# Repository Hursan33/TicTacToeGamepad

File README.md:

# TicTacToeGamepad

## TBD 
Test new version of code, assemble the integrated arduino version, upload edited case

## 1 Introduction
This project is an implementation of a Tic Tac Toe game using both hardware and software. The
purpose of the project was to practice working with an 8-bit mcu on register level, but I worked on it more and created a standalone version.
## 2 Materials and technologies
* MCU (I used Avr curiosity nano for school and an Arduino pro micro for standalone)  
* 9x Keyboard switches  
* 9x SK6812MINI-E LEDs  
* 3x 100uF capacitors  
* 1x 330r resistor  
  
The game itself is played on a 3x3 playing field made from keyboard switches, which are soldered onto
a PCB I designed. The PCB sits in a 3D printed case.

## 2 Functions
The game uses addressable LEDs to show the board state. Each player has their own color, which is
shown on the fields the player has occupied. After the game is over, whether it was a draw or a player
won, there is an animation and 5 second delay, after which the game restarts. The first player to act
is decided by which player won the last game, or which player went last. There are 2 possible game
modes:  

* Classic  
* 3-mark rule  

Both game modes can be played in single player, which replaces the second player with a bot.
### 2.1 Classic
This game mode uses the classic rules of a 3x3 tic tac toe game. The player wins by putting 3 marks
in a row, column or diagonal. After the board is filled and no player has won, the game is declared as
a draw.
1
### 2.2 3-mark rule
Here each player only gets 3 marks. After that they must move their oldest mark to a new position.
In this game mode there is no draw, a player must win to end the game. The moving mark is shown
by being dimmer than the rest.
### 2.3 Bot
The bot uses a simple algorithm to decide which space it wants to occupy.
1. Checks if a win is possible, then it places the mark there.  
2. Checks if the player can win, then it blocks the player.  
3. If the center is free, it puts the mark there.  
4. Checks every corner in a random order and occupies it if possible.  
5. Checks every side field in a random order and occupies it if possible.

In the 3-mark rule, when checking if the player can win, it also remembers which mark the player is
moving. This ensures that the bot blocks the correct field.
### 3.4 Ending animation
After the game ends, either by a player winning or a draw, there is an animation played. The animation
lights up the LEDs in a “2” shape with the color of the winning player, or in the case of a draw with
the “draw” color.
## 3 Costumizations
There are a few customizations in the game. First, the game mode and if the bot is active can be
set. The colors of each player and draw are also customizable, using RGB format. The dimness of the
moving mark is also possible to change.
To change these settings these macros can be modified in the “config.h” file:

* GAME_MODE – 1 (3-mark rule) or 0 (Classic).  
* BOT – 1 (Bot is turned on) or 0 (Bot is off).  
* PLAYER_N_COLOR and DRAW_COLOR – has this syntax (Color) R, G, B, you replace the R, G, B
with the corresponding colors of the value. Player colors and draw color all have to be different
otherwise an error occurs.  
* DIM_DIV – the amount by which the values of the color are divided, e.g. DIM_DIV 16 makes the
LEDs be 1
16 of their brightness.  

If there were changes to any of the settings the game can be simply re-flashed onto the mcu by using
the Makefile in the project folder.
### 3.1 Error
If an error occurs, the board starts blinking red. In case this happens check your color values, because
some of them have the same values.
## Schematic and PCB

The gerber files for the PCB are present in the repository.
## PINOUT

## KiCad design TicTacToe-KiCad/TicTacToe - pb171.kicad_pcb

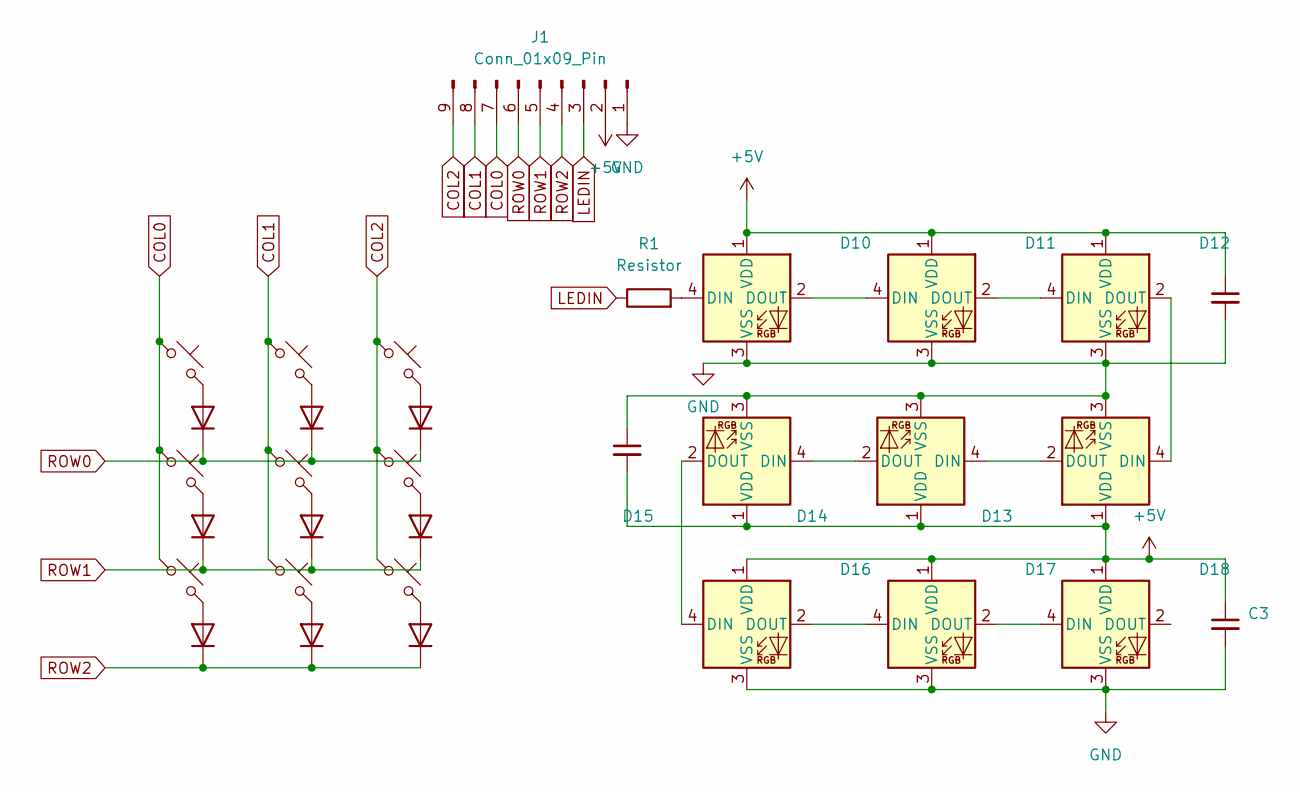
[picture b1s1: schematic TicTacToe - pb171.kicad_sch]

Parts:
C1, C2, C3: C_Small; C_1206_3216Metric
D1, D2, D3, D4, D5, D6, D7, D8, D9: D; D_SOD-123
D10, D11, D12, D13, D14, D15, D16, D17, D18: LED_WS2812B; SK6812-MINI-E
J1: Conn_01x09_Pin; PinHeader_1x09_P2.54mm_Horizontal
R1: Resistor; Resistor_1206
S1, S2, S3, S4, S5, S6, S7, S8, S9: Keyswitch; Choc_V1_1.00u

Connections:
+5V: C1.1, C2.2, C3.1, D10.1 (VDD), D11.1 (VDD), D12.1 (VDD), D13.1 (VDD), D14.1 (VDD), D15.1 (VDD), D16.1 (VDD), D17.1 (VDD), D18.1 (VDD), J1.2
COL0: J1.7, S1.1, S4.1, S7.1
COL1: J1.8, S2.1, S5.1, S8.1
COL2: J1.9, S3.1, S6.1, S9.1
GND: C1.2, C2.1, C3.2, D10.3 (VSS), D11.3 (VSS), D12.3 (VSS), D13.3 (VSS), D14.3 (VSS), D15.3 (VSS), D16.3 (VSS), D17.3 (VSS), D18.3 (VSS), J1.1
LEDIN: J1.3, R1.1
unnamed: D1.2 (A), S1.2
unnamed: D2.2 (A), S2.2
unnamed: D3.2 (A), S3.2
unnamed: D4.2 (A), S4.2
unnamed: D5.2 (A), S5.2
unnamed: D6.2 (A), S6.2
unnamed: D7.2 (A), S7.2
unnamed: D8.2 (A), S8.2
unnamed: D9.2 (A), S9.2
unnamed: D10.4 (DIN), R1.2
unnamed: D10.2 (DOUT), D11.4 (DIN)
unnamed: D11.2 (DOUT), D12.4 (DIN)
unnamed: D12.2 (DOUT), D13.4 (DIN)
unnamed: D13.2 (DOUT), D14.4 (DIN)
unnamed: D14.2 (DOUT), D15.4 (DIN)
unnamed: D15.2 (DOUT), D16.4 (DIN)
unnamed: D16.2 (DOUT), D17.4 (DIN)
unnamed: D17.2 (DOUT), D18.4 (DIN)
ROW0: D1.1 (K), D2.1 (K), D3.1 (K), J1.6
ROW1: D4.1 (K), D5.1 (K), D6.1 (K), J1.5
ROW2: D7.1 (K), D8.1 (K), D9.1 (K), J1.4

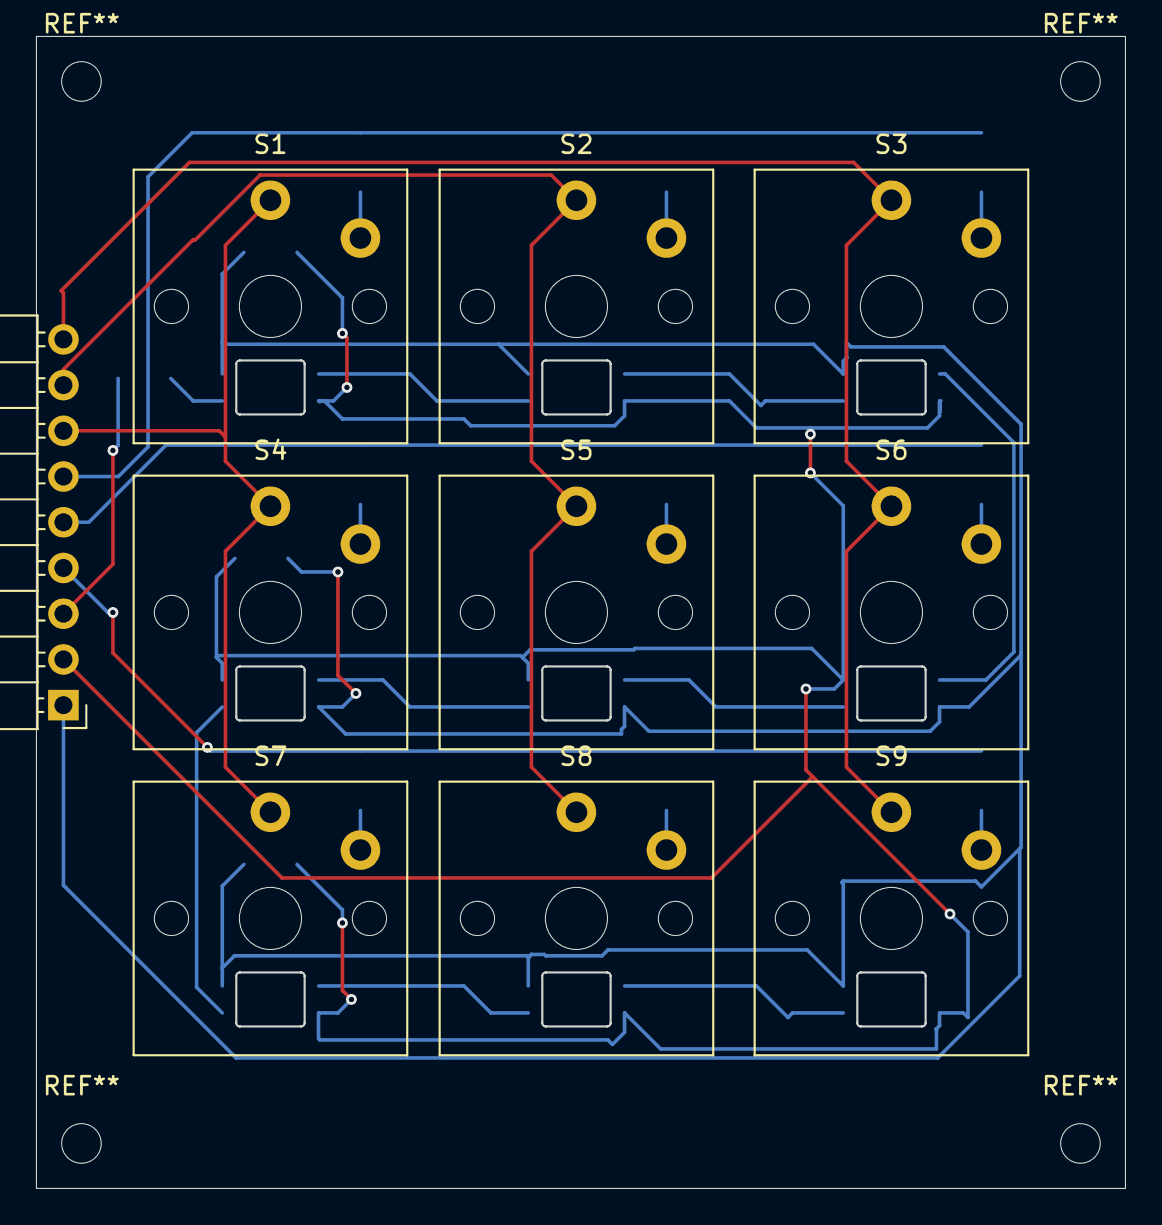
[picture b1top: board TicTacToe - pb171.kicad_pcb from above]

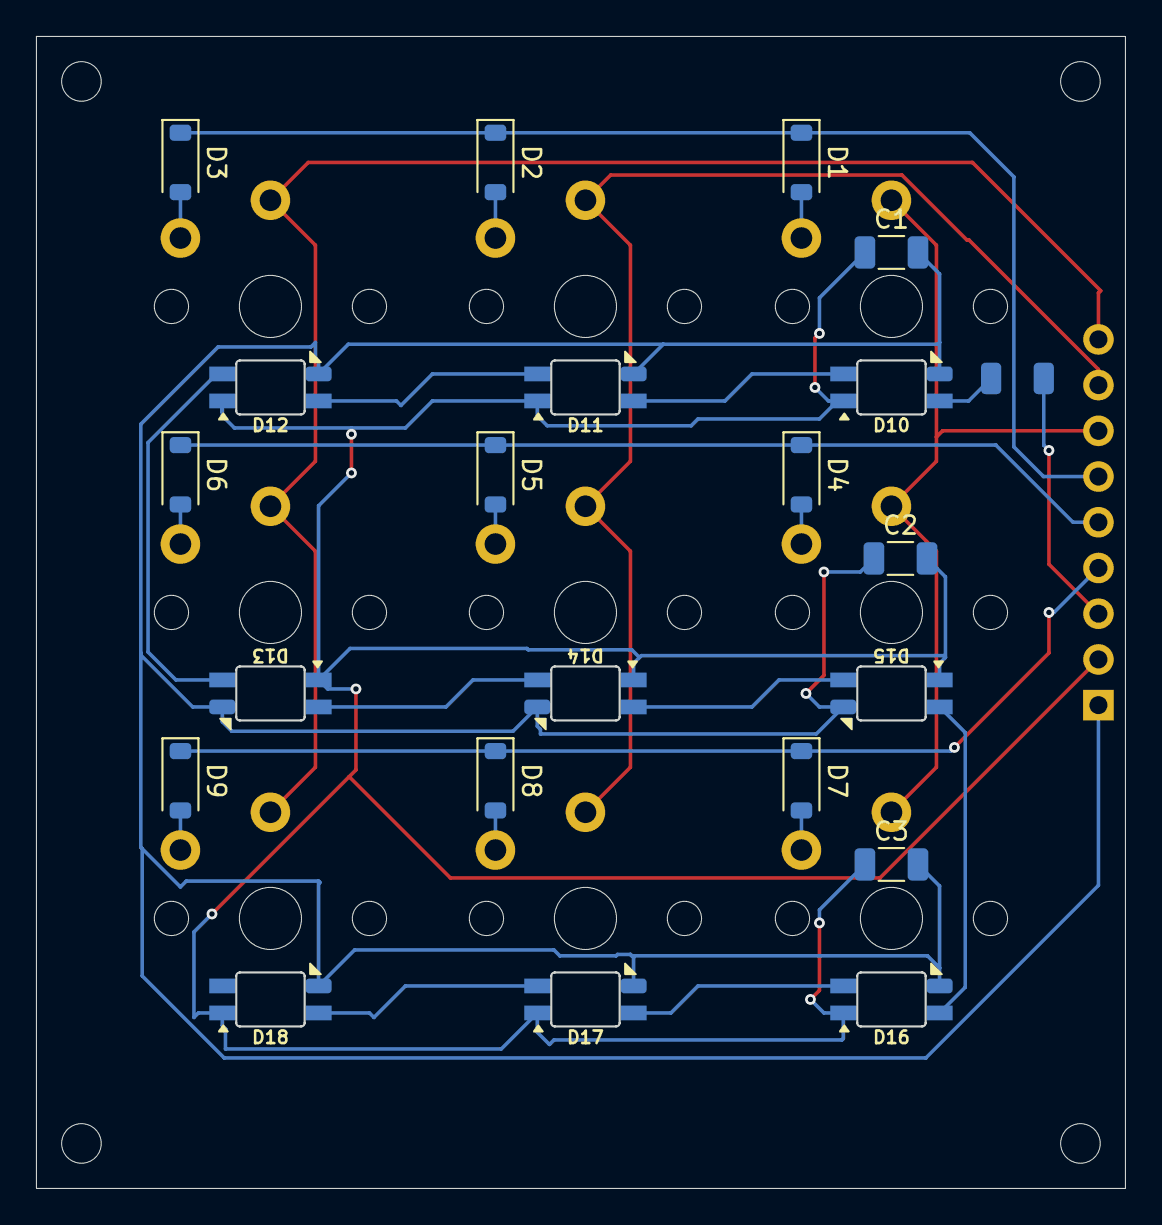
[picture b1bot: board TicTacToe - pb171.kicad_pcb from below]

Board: 2 copper layers, 60.4 x 63.9 mm, 32 parts (22 on the bottom side), 27 nets.

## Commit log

2025-06-01 Feat: uploaded source code and README for AVR curiosity nano board
2025-06-02 Added gitignore
2025-06-02 updated .gitignore and removed tracking for build folders
2025-06-02 Added arduino uno version of code | compiles, but have not tested on hardware | edited formattin
2025-06-05 Updated few lines in arduino version
2025-06-05 Added gerber file for PCB
2025-06-05 Added KiCad project
2025-06-15 Updated formatting of readme and added model for AvrCuriosity version
2025-06-15 Exchanged step file for stl
2025-06-15 Forgot to push file
2025-06-15 Once again switched formats, so it keeps multiple parts
2025-07-19 Added standalone stuff
2025-07-19 Almost done
2025-07-19 Added 3d model for keypad
2025-07-19 Tracking mp4 files with git lfs
2025-07-19 Added demo videos
